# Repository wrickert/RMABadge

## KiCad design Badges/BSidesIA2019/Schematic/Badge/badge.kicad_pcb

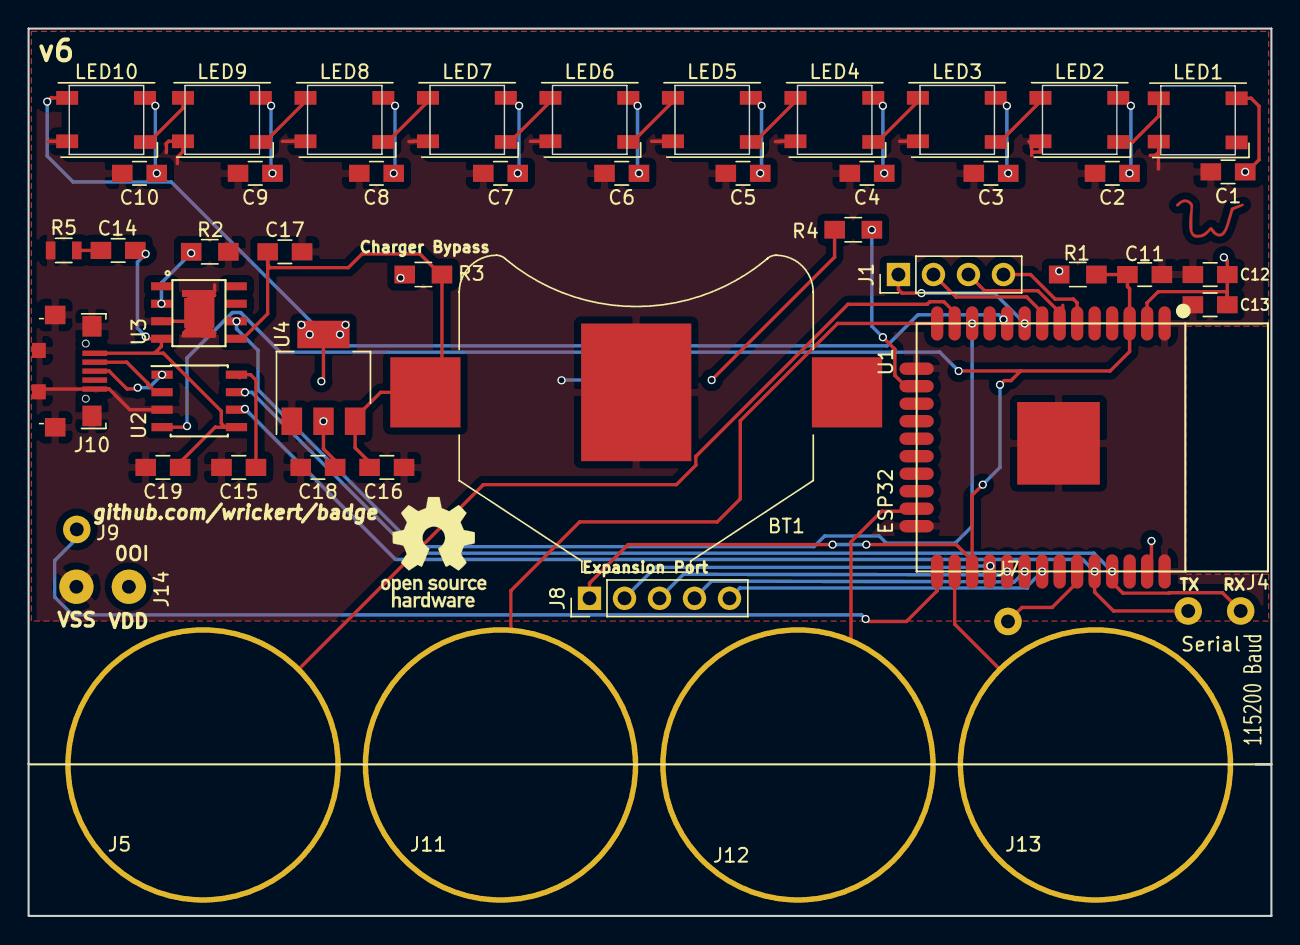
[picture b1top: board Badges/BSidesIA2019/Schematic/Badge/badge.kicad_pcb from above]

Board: 2 copper layers, 90.2 x 64.4 mm, 52 parts (1 on the bottom side), 39 nets.

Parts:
BT1: Battery_Cell; Keystone_3008_1x2450-CoinCell
C1, C2, C3, C4, C5, C6, C7, C8, C9, C10, C11, C12, C15, C19: 0.1uF; C_0805_HandSoldering
C13, C14, C17: 10uF; C_0805_HandSoldering
C16, C18: 1uF; C_0805_HandSoldering
J1: Left2; Pin_Header_Straight_1x04_Pitch2.54mm
J4: Serial; SolderWirePad_2x_1mmDrill
J5: Penny3; Penny
J7: Right2; SolderWirePad_single_1mmDrill
J8: Right3; Pin_Header_Straight_1x05_Pitch2.54mm
J9: Right4; SolderWirePad_single_1mmDrill
J10: USB_B_Micro; USB_Micro-B_Jing
J11: Penny2; Penny
J12: Penny1; Penny
J13: Penny0; Penny
J14: Power; SolderWirePad_2x_1mmDrill
LED1, LED2, LED3, LED4, LED5, LED6, LED7, LED8, LED9, LED10: WS2812B; WS2812B-Sunken
LS1: PKMCS0909E4000-R1; XDCR_PKMCS0909E4000-R1
R1: 10k; R_0805_HandSoldering
R2: 1k; R_0805_HandSoldering
R3: 0ohm; R_0805_HandSoldering
R4: 22ohm; R_0805_HandSoldering
R5: 1.5; R_0805
Ref**: Val**; W
U1: ESP32-WROOM
U2: otter_CH330; SOIC-8_3.9x4.9mm_Pitch1.27mm
U3: HX4056
U4: TLV1117-33; SOT-223-3_TabPin2

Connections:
IO0: J9.1, U1.25
IO5: J8.3, U1.29
IO13: R4.1, U1.16
IO17: J8.2, U1.28
IO18: J8.4, U1.30
IO19: J8.5, U1.31
IO21: J7.1, U1.33
IO27: U1.12, U3.6
IO32: J1.2, U1.8
IO33: J1.1, U1.9
IO34: J1.4, U1.6
IO35: J1.3, U1.7
unnamed: C14.1, R5.2
unnamed: C15.1, U2.8
unnamed: J10.2, U2.2
unnamed: J10.3, U2.1
unnamed: LED1.2, LED2.4
unnamed: LED2.2, LED3.4
unnamed: LED3.2, LED4.4
unnamed: LED4.2, LED5.4
unnamed: LED5.2, LED6.4
unnamed: LED6.2, LED7.4
unnamed: LED7.2, LED8.4
unnamed: LED8.2, LED9.4
unnamed: LED9.2, LED10.4
unnamed: LS1.1, R4.2
unnamed: R2.1, U3.2
P0: J13.1, U1.26
P1: J12.1, U1.23
P2: J11.1, U1.14
P3: J5.1, U1.13
RTS: C11.1, J8.1, R1.2, U1.3, U1.27, U2.4
RX: J4.1, U1.35, U2.7
SPI: LED10.2, U1.10
TX: J4.1, U1.34, U2.6
VBUS: C14.2, C19.2, J10.1, U2.5, U3.4
VDD: C1.1, C2.1, C3.1, C4.1, C5.1, C6.1, C7.1, C8.1, C9.1, C10.1, C12.2, C13.2, C18.1, J14.1, LED1.1, LED2.1, LED3.1, LED4.1, LED5.1, LED6.1, LED7.1, LED8.1, LED9.1, LED10.1, R1.1, R3.1, U1.2, U4.2
VDDA: BT1.1, C16.1, C17.2, R3.2, U3.5, U4.3
VSS: BT1.2, C1.2, C2.2, C3.2, C4.2, C5.2, C6.2, C7.2, C8.2, C9.2, C10.2, C11.2, C12.1, C13.1, C15.2, C16.2, C17.1, C18.2, C19.1, J10.5, J10.6, J14.1, LED1.3, LED2.3, LED3.3, LED4.3, LED5.3, LED6.3, LED7.3, LED8.3, LED9.3, LED10.3, LS1.2, R2.2, R5.1, U1.1, U1.15, U1.24, U1.38, U1.39, U2.3, U3.3, U3.9, U4.1

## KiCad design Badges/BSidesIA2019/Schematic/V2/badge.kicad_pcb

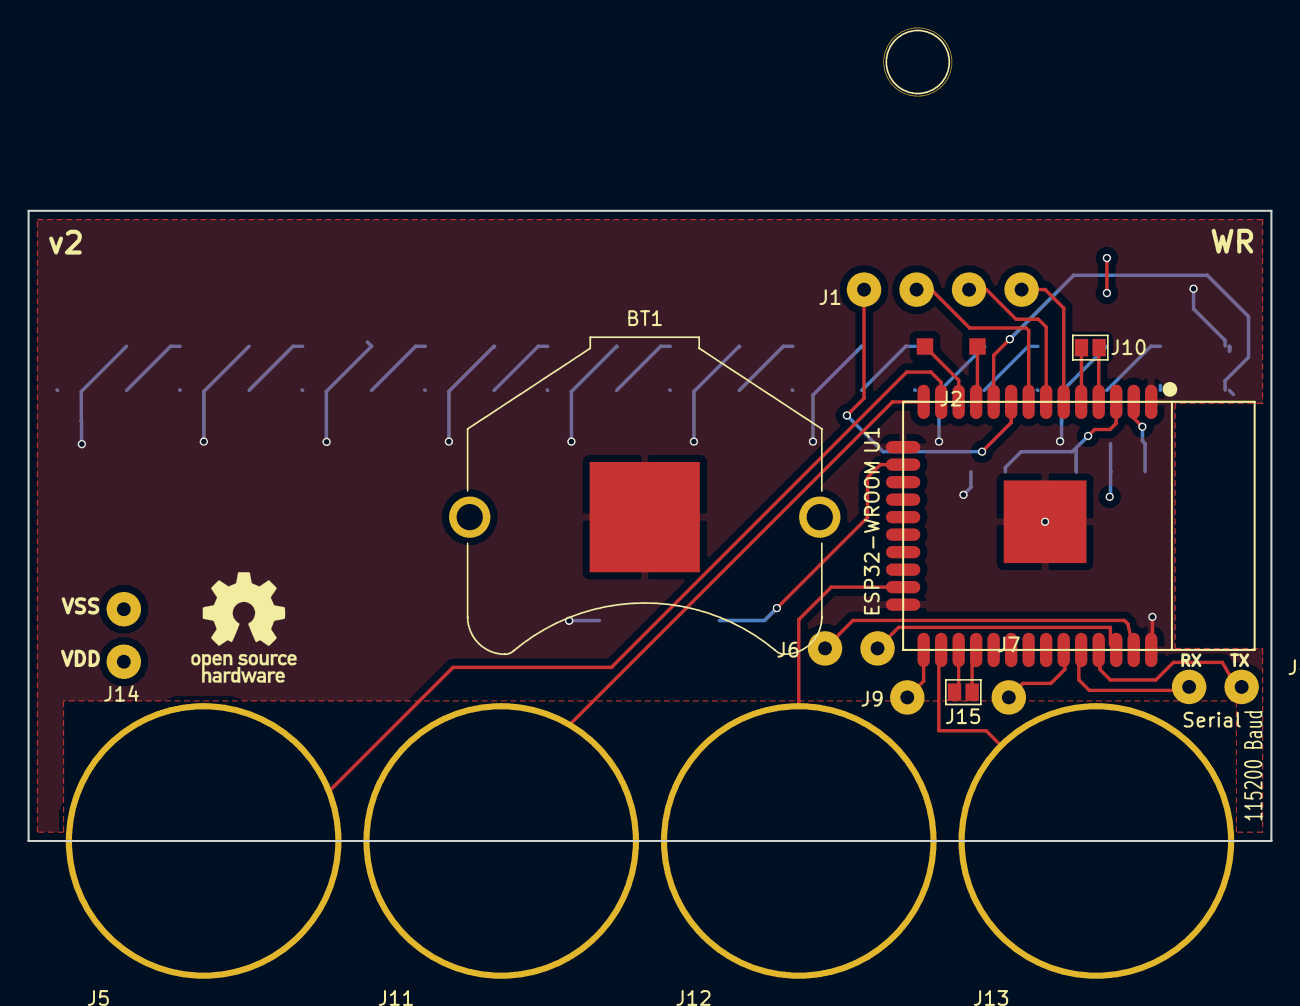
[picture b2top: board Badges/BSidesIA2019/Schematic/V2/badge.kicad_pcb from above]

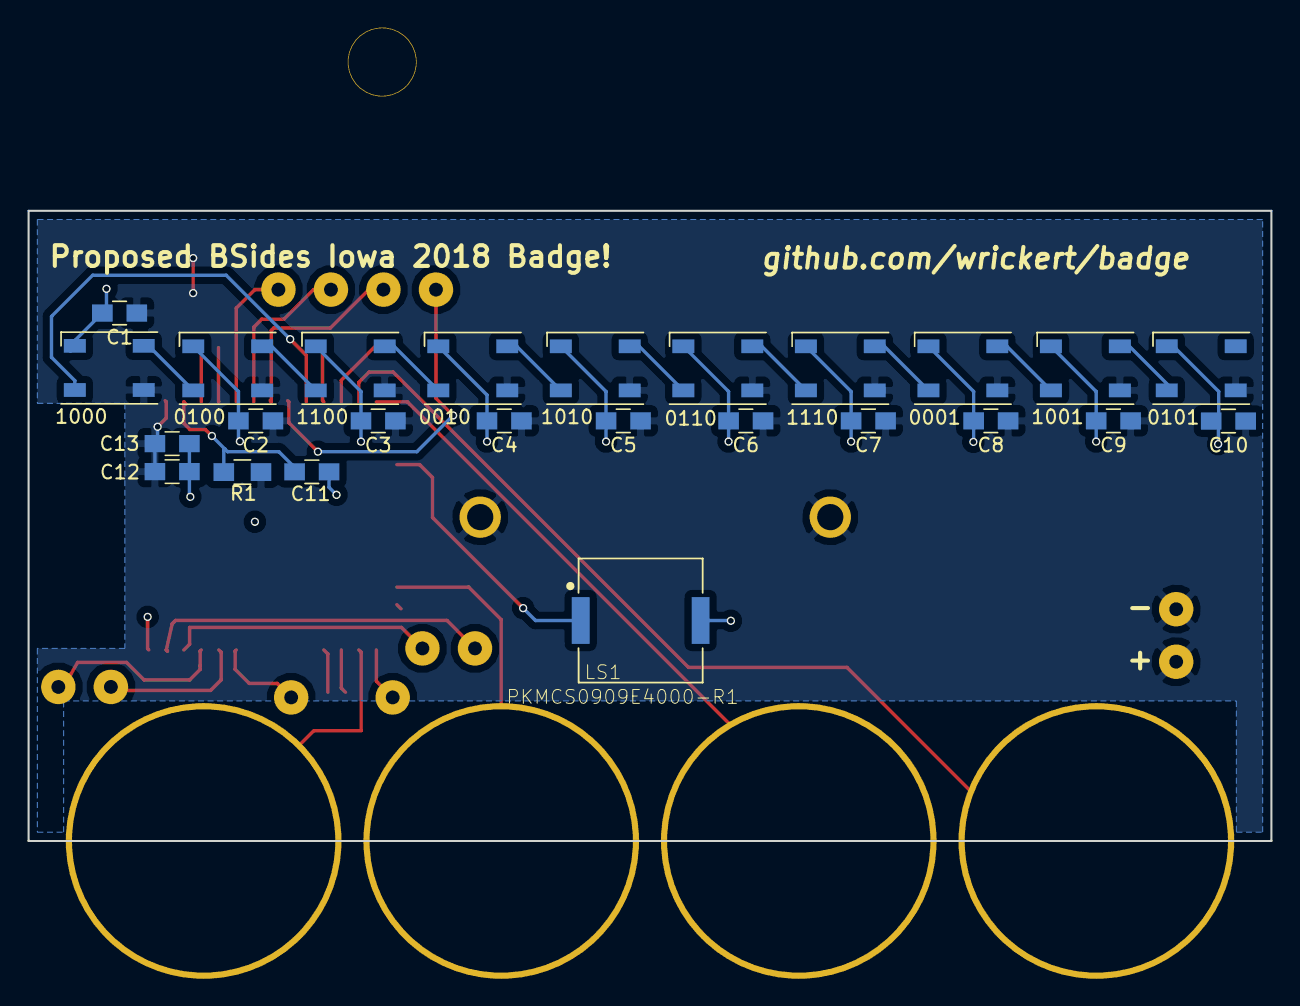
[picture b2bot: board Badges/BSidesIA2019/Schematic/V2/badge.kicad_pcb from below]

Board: 2 copper layers, 90.2 x 45.7 mm, 40 parts (25 on the bottom side), 35 nets.

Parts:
0001, 0010, 0100, 0101, 0110, 1000, 1001, 1010, 1100, 1110: WS2812B; LED_WS2812B-PLCC4
BT1: Battery_Cell; Keystone_3009_1x2450-CoinCell
C1, C2, C3, C4, C5, C6, C7, C8, C9, C10, C11, C12: 0.1uF; C_0805_HandSoldering
C13: 10uF; C_0805_HandSoldering
J1: Left2; SolderWirePad_4xInline_1mmDrill
J2: Left3; SolderWirePad_2x_1mmDrill
J4: Serial; SolderWirePad_2x_1mmDrill
J5: Penny3; Penny
J6: Right1; SolderWirePad_2x_1mmDrill
J7: Right2; SolderWirePad_single_1mmDrill
J9: Right4; SolderWirePad_single_1mmDrill
J10: Left1; GS2
J11: Penny2; Penny
J12: Penny1; Penny
J13: Penny0; Penny
J14: Power; SolderWirePad_2x_1mmDrill
J15: Right5; GS2
LS1: PKMCS0909E4000-R1; XDCR_PKMCS0909E4000-R1
R1: 10k; R_0805_HandSoldering
U1: ESP32-WROOM

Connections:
GND: C12.1, C13.1
IO0: J9.1, U1.25
IO13: LS1.1, U1.16
IO16: J15.2, U1.27
IO17: J15.1, U1.28
IO21: J7.1, U1.33
IO22: J6.1, U1.36
IO23: J6.1, U1.37
IO26: J2.1, U1.11
IO27: J2.1, U1.12
IO32: J1.1, U1.8
IO33: J1.1, U1.9
IO34: J1.1, U1.6
IO35: J1.1, U1.7
unnamed: C11.1, R1.2, U1.3
unnamed: 0100.4, 1000.2
unnamed: 0100.2, 1100.4
unnamed: 0010.4, 1100.2
unnamed: 0010.2, 1010.4
unnamed: 0110.4, 1010.2
unnamed: 0110.2, 1110.4
unnamed: 0001.4, 1110.2
unnamed: 0001.2, 1001.4
unnamed: 0101.4, 1001.2
P0: J13.1, U1.26
P1: J12.1, U1.23
P2: J11.1, U1.14
P3: J5.1, U1.13
RX: J4.1, U1.34
SPI: 1000.4, U1.10
TX: J4.1, U1.35
VDD: 0001.1, 0010.1, 0100.1, 0101.1, 0110.1, 1000.1, 1001.1, 1010.1, 1100.1, 1110.1, BT1.1, C1.1, C2.1, C3.1, C4.1, C5.1, C6.1, C7.1, C8.1, C9.1, C10.1, C12.2, C13.2, J14.1, R1.1, U1.2
VN: J10.1, U1.5
VP: J10.2, U1.4
VSS: 0001.3, 0010.3, 0100.3, 0101.3, 0110.3, 1000.3, 1001.3, 1010.3, 1100.3, 1110.3, BT1.2, C1.2, C2.2, C3.2, C4.2, C5.2, C6.2, C7.2, C8.2, C9.2, C10.2, C11.2, LS1.2, U1.1, U1.15, U1.24, U1.38, U1.39

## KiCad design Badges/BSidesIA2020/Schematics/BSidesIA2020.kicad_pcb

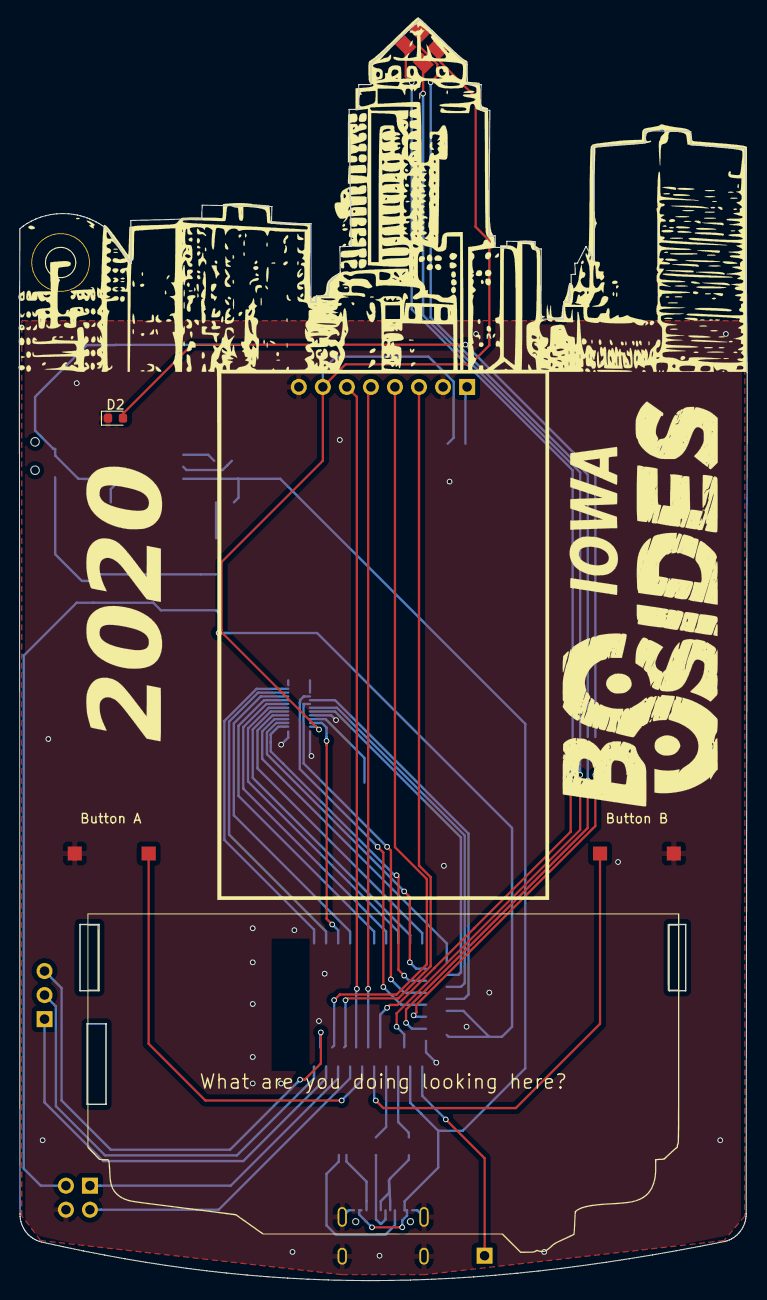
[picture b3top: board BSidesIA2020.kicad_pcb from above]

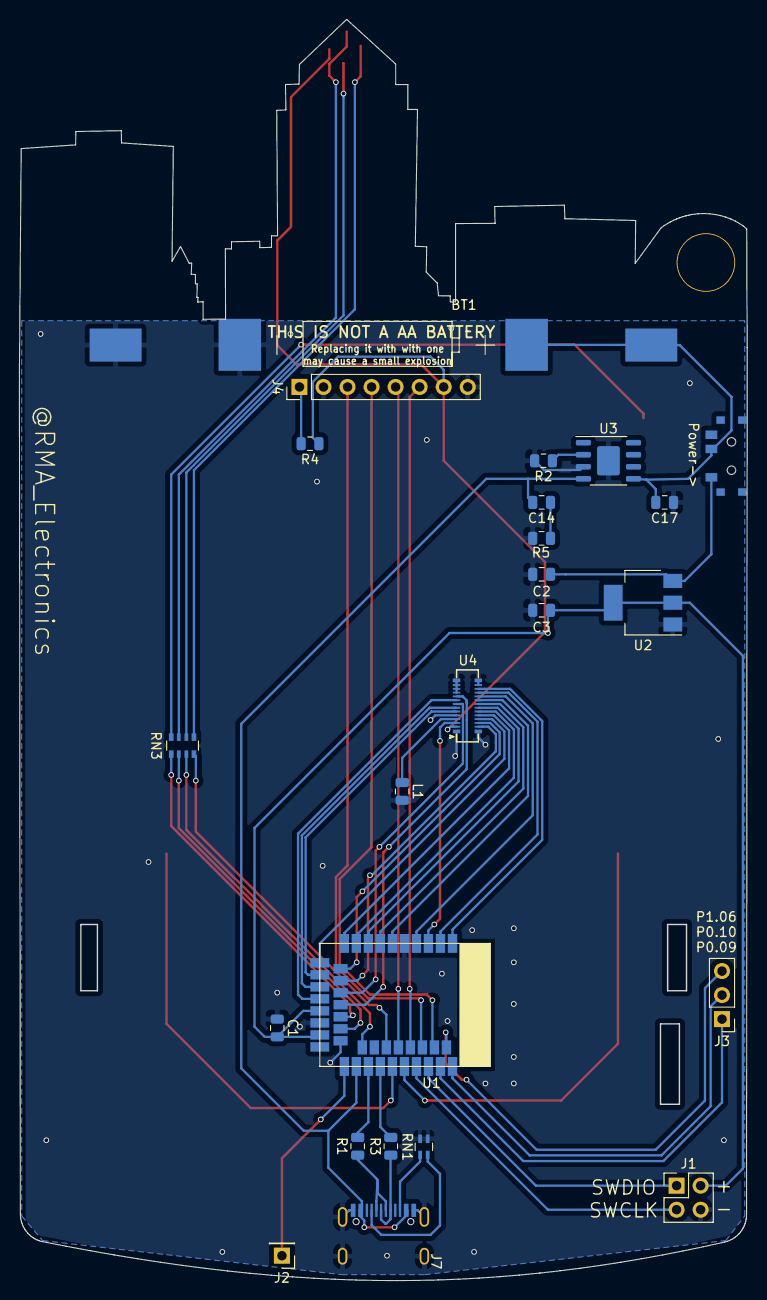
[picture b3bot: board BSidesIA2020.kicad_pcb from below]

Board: 2 copper layers, 76.9 x 133.3 mm, 28 parts (24 on the bottom side), 52 nets.

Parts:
BT1: Battery_Cell; Dongguan14500
Button A: SW_DIP_x01; 1TS002E-2500-2500-CT-HYP-Button
Button B: SW_DIP_x01; 1TS002E-2500-2500-CT-HYP-Button
C1: 4.7uF; C_0805_2012Metric
C2, C3: 1uF; C_0805_2012Metric
C14, C17: 10uF; C_0805_2012Metric
D1: LED_BGRA; EKINGLUX-E6
D2: LED; LED_0603_1608Metric
J1: Conn_02x02_Odd_Even; PinHeader_2x02_P2.54mm_Vertical
J2: Conn_01x01; PinHeader_1x01_P2.54mm_Vertical
J3: Conn_01x03; PinHeader_1x03_P2.54mm_Vertical
J4: Conn_01x08; PinHeader_1x08_P2.54mm_Vertical
J7: USB_C_Receptacle; USB_C_Receptical-Jing
L1: L_Small; L_0805_2012Metric
Power->: SW3; SK-3296S_switch
R1, R3: 27Ohm; R_0805_2012Metric
R2: 1k; R_0805_2012Metric
R4: R_Small; R_0805_2012Metric
R5: 1.5; R_0805_2012Metric
RN1: 10k; R_Array_Concave_2x0603
RN3: 270; R_Array_Convex_4x0603
U1: E73-2G4M08S1C
U2: TLV1117-33; SOT-223-3_TabPin2
U3: HX4056; HSOP-8-1EP_3.9x4.9mm_P1.27mm_EP2.41x3.1mm
U4: BBQ10KBD; BM14B(0.8)-24DS-0.4V(53)

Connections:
+5V: C14.2, J7.A4, J7.A9, J7.B4, J7.B9, U1.27, U3.4
Attention: RN3.1, U1.20
Blue: RN3.4, U1.32
ButtonA: Button A.2, U1.35
ButtonB: Button B.2, U1.33
COL1: U1.15, U4.7
COL2: U1.17, U4.9
COL3: U1.18, U4.10
COL4: U1.1, U4.17
COL5: U1.4, U4.19
D+: J7.A6, J7.B6, R3.1
D-: J7.A7, J7.B7, R1.1
DC: J4.3, U1.38
Green: RN3.3, U1.28
LEDA1: U1.12, U4.26
LEDA2: U1.10, U4.24
LEDK1: U1.11, U4.25
LEDK2: U1.9, U4.23
MIC: U1.3, U4.3
unnamed: C14.1, R5.2
unnamed: D1.1, RN3.5
unnamed: D1.2, RN3.6
unnamed: D1.3, RN3.7
unnamed: D2.2, RN3.8
unnamed: J2.1, U1.26
unnamed: J3.1, U1.41
unnamed: J3.2, U1.43
unnamed: J3.3, U1.42
unnamed: J4.1, R4.2
unnamed: J7.A5, RN1.2
unnamed: J7.B5, RN1.1
unnamed: L1.1, U4.4
unnamed: R1.2, U1.29
unnamed: R2.1, U3.2
unnamed: R3.2, U1.31
ROW1: U1.13, U4.6
ROW2: U1.16, U4.8
ROW3: U1.2, U4.18
ROW4: U1.6, U4.20
ROW5: U1.7, U4.21
ROW6: U1.8, U4.22
ROW7: U1.14, U4.27
RST: J4.4, U1.40
Red: RN3.2, U1.22
SCL: J4.6, U1.36
SDA: J4.5, U1.34
SWCLK: J1.1, U1.39
SWDIO: J1.3, U1.37
VCC: C1.2, C3.2, D1.4, J1.2, J4.7, R4.1, U1.19, U1.23, U2.2, U4.2
VDD: C2.2, Power->.3, U2.3
VDDA: BT1.1, C17.2, Power->.2, U3.5
VSS: BT1.2, Button A.1, Button B.1, C1.1, C2.1, C3.1, C17.1, D2.1, J1.4, J4.2, J4.8, J7.A1, J7.A12, J7.B1, J7.B12, J7.S1, L1.2, R2.2, R5.1, RN1.3, RN1.4, U1.5, U1.21, U1.24, U2.1, U3.3, U3.9, U4.1, U4.5, U4.11, U4.12, U4.13, U4.14, U4.15, U4.16, U4.28

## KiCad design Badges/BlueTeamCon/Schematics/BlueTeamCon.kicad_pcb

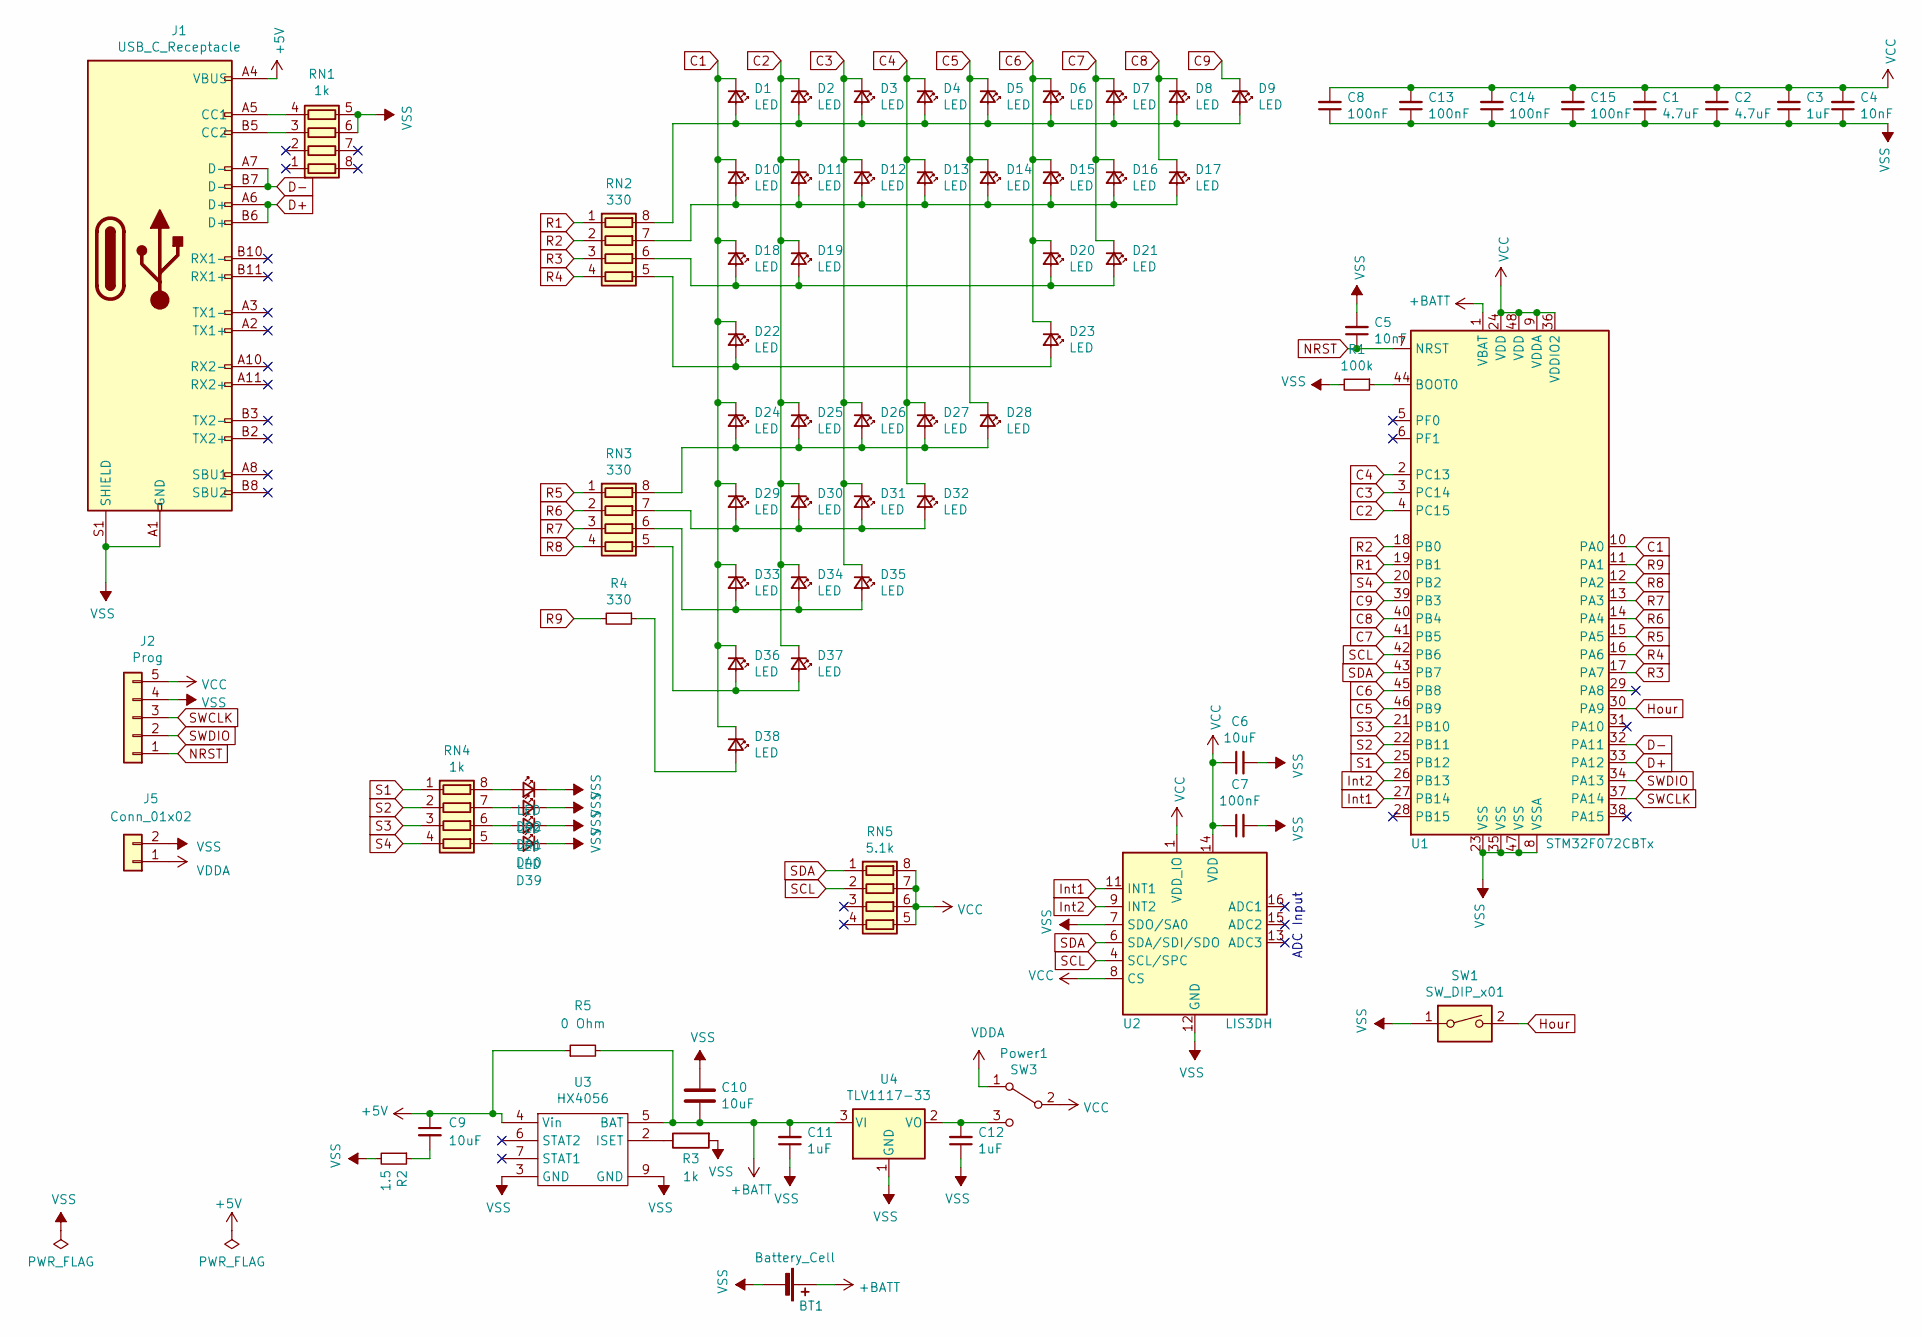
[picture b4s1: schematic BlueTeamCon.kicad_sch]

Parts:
BT1: Battery_Cell; Dongguan14500
C1, C2: 4.7uF; C_0805_2012Metric
C3, C11, C12: 1uF; C_0805_2012Metric
C4, C5: 10nF; C_0805_2012Metric
C6, C9, C10: 10uF; C_0805_2012Metric
C7, C8, C13, C14, C15: 100nF; C_0805_2012Metric
D1, D2, D3, D4, D5, D6, D7, D8, D9, D10, D11, D12, D13, D14, D15, D16, D17, D18, D19, D20, D21, D22, D23, D24, D25, D26, D27, D28, D29, D30, D31, D32, D33, D34, D35, D36, D37, D38: LED; LED_0805_2012Metric
D39, D40, D41, D42: LED; T776-ReverseMountLED
J1: USB_C_Receptacle; USB_C_Receptical-Jing
J2: Prog; PinHeader_1x05_P2.54mm_Vertical
J5: Conn_01x02; PinHeader_1x02_P2.54mm_Vertical
Power1: SW3; SK-3296S_switch
R1: 100k; R_0805_2012Metric
R2: 1.5; R_0805_2012Metric
R3: 1k; R_0805_2012Metric
R4: 330; R_0805_2012Metric
R5: 0 Ohm; R_0805_2012Metric
RN1, RN4: 1k; R_Array_Convex_4x0603
RN2, RN3: 330; R_Array_Convex_4x0603
RN5: 5.1k; R_Array_Convex_4x0603
SW1: SW_DIP_x01; SW_SPST_SKQG_WithStem
U1: STM32F072CBTx; LQFP-48_7x7mm_P0.5mm
U2: LIS3DH; LGA-16_3x3mm_P0.5mm_LayoutBorder3x5y
U3: HX4056; HTSOP-8-1EP_3.9x4.9mm_P1.27mm_EP2.4x3.2mm
U4: TLV1117-33; SOT-223-3_TabPin2

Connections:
+5V: C9.1, J1.A4 (VBUS), J1.A9 (VBUS), J1.B4 (VBUS), J1.B9 (VBUS), R5.1, U3.4 (Vin)
+BATT: BT1.1 (+), C10.2, C11.2, R5.2, U1.1 (VBAT), U3.5 (BAT), U4.3 (VI)
C1: D1.1 (K), D10.1 (K), D18.1 (K), D22.1 (K), D24.1 (K), D29.1 (K), D33.1 (K), D36.1 (K), D38.1 (K), U1.10 (PA0)
C2: D2.1 (K), D11.1 (K), D19.1 (K), D25.1 (K), D30.1 (K), D34.1 (K), D37.1 (K), U1.4 (PC15)
C3: D3.1 (K), D12.1 (K), D26.1 (K), D31.1 (K), D35.1 (K), U1.3 (PC14)
C4: D4.1 (K), D13.1 (K), D27.1 (K), D32.1 (K), U1.2 (PC13)
C5: D5.1 (K), D14.1 (K), D28.1 (K), U1.46 (PB9)
C6: D6.1 (K), D15.1 (K), D20.1 (K), D23.1 (K), U1.45 (PB8)
C7: D7.1 (K), D16.1 (K), D21.1 (K), U1.41 (PB5)
C8: D8.1 (K), D17.1 (K), U1.40 (PB4)
C9: D9.1 (K), U1.39 (PB3)
D+: J1.A6 (D+), J1.B6 (D+), U1.33 (PA12)
D-: J1.A7 (D-), J1.B7 (D-), U1.32 (PA11)
Hour: SW1.2, U1.30 (PA9)
Int1: U1.27 (PB14), U2.11 (INT1)
Int2: U1.26 (PB13), U2.9 (INT2)
NRST: C5.1, J2.1, U1.7 (NRST)
unnamed: C9.2, R2.1
unnamed: C12.2, Power1.3 (C), U4.2 (VO)
unnamed: D1.2 (A), D2.2 (A), D3.2 (A), D4.2 (A), D5.2 (A), D6.2 (A), D7.2 (A), D8.2 (A), D9.2 (A), RN2.8 (R1.2)
unnamed: D10.2 (A), D11.2 (A), D12.2 (A), D13.2 (A), D14.2 (A), D15.2 (A), D16.2 (A), D17.2 (A), RN2.7 (R2.2)
unnamed: D18.2 (A), D19.2 (A), D20.2 (A), D21.2 (A), RN2.6 (R3.2)
unnamed: D22.2 (A), D23.2 (A), RN2.5 (R4.2)
unnamed: D24.2 (A), D25.2 (A), D26.2 (A), D27.2 (A), D28.2 (A), RN3.8 (R1.2)
unnamed: D29.2 (A), D30.2 (A), D31.2 (A), D32.2 (A), RN3.7 (R2.2)
unnamed: D33.2 (A), D34.2 (A), D35.2 (A), RN3.6 (R3.2)
unnamed: D36.2 (A), D37.2 (A), RN3.5 (R4.2)
unnamed: D38.2 (A), R4.1
unnamed: D39.2 (A), RN4.5 (R4.2)
unnamed: D40.2 (A), RN4.6 (R3.2)
unnamed: D41.2 (A), RN4.7 (R2.2)
unnamed: D42.2 (A), RN4.8 (R1.2)
unnamed: J1.A5 (CC1), RN1.4 (R4.1)
unnamed: J1.B5 (CC2), RN1.3 (R3.1)
unnamed: R1.1, U1.44 (BOOT0)
unnamed: R3.1, U3.2 (ISET)
R1: RN2.1 (R1.1), U1.19 (PB1)
R2: RN2.2 (R2.1), U1.18 (PB0)
R3: RN2.3 (R3.1), U1.17 (PA7)
R4: RN2.4 (R4.1), U1.16 (PA6)
R5: RN3.1 (R1.1), U1.15 (PA5)
R6: RN3.2 (R2.1), U1.14 (PA4)
R7: RN3.3 (R3.1), U1.13 (PA3)
R8: RN3.4 (R4.1), U1.12 (PA2)
R9: R4.2, U1.11 (PA1)
S1: RN4.1 (R1.1), U1.25 (PB12)
S2: RN4.2 (R2.1), U1.22 (PB11)
S3: RN4.3 (R3.1), U1.21 (PB10)
S4: RN4.4 (R4.1), U1.20 (PB2)
SCL: RN5.2 (R2.1), U1.42 (PB6), U2.4 (SCL/SPC)
SDA: RN5.1 (R1.1), U1.43 (PB7), U2.6 (SDA/SDI/SDO)
SWCLK: J2.3, U1.37 (PA14)
SWDIO: J2.2, U1.34 (PA13)
VCC: C1.2, C2.2, C3.2, C4.2, C6.1, C7.1, C8.2, C13.2, C14.2, C15.2, J2.5, Power1.2 (B), RN5.5 (R4.2), RN5.6 (R3.2), RN5.7 (R2.2), RN5.8 (R1.2), U1.9 (VDDA), U1.24 (VDD), U1.36 (VDDIO2), U1.48 (VDD), U2.1 (VDD_IO), U2.8 (CS), U2.14 (VDD)
VDDA: J5.1, Power1.1 (A)
VSS: BT1.2 (-), C1.1, C2.1, C3.1, C4.1, C5.2, C6.2, C7.2, C8.1, C10.1, C11.1, C12.1, C13.1, C14.1, C15.1, D39.1 (K), D40.1 (K), D41.1 (K), D42.1 (K), J1.A1 (GND), J1.A12 (GND), J1.B1 (GND), J1.B12 (GND), J1.S1 (SHIELD), J2.4, J5.2, R1.2, R2.2, R3.2, RN1.5 (R4.2), RN1.6 (R3.2), SW1.1, U1.8 (VSSA), U1.23 (VSS), U1.35 (VSS), U1.47 (VSS), U2.5 (GND), U2.7 (SDO/SA0), U2.10 (GND), U2.12 (GND), U3.3 (GND), U3.9 (GND), U4.1 (GND)

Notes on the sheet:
ADC Input

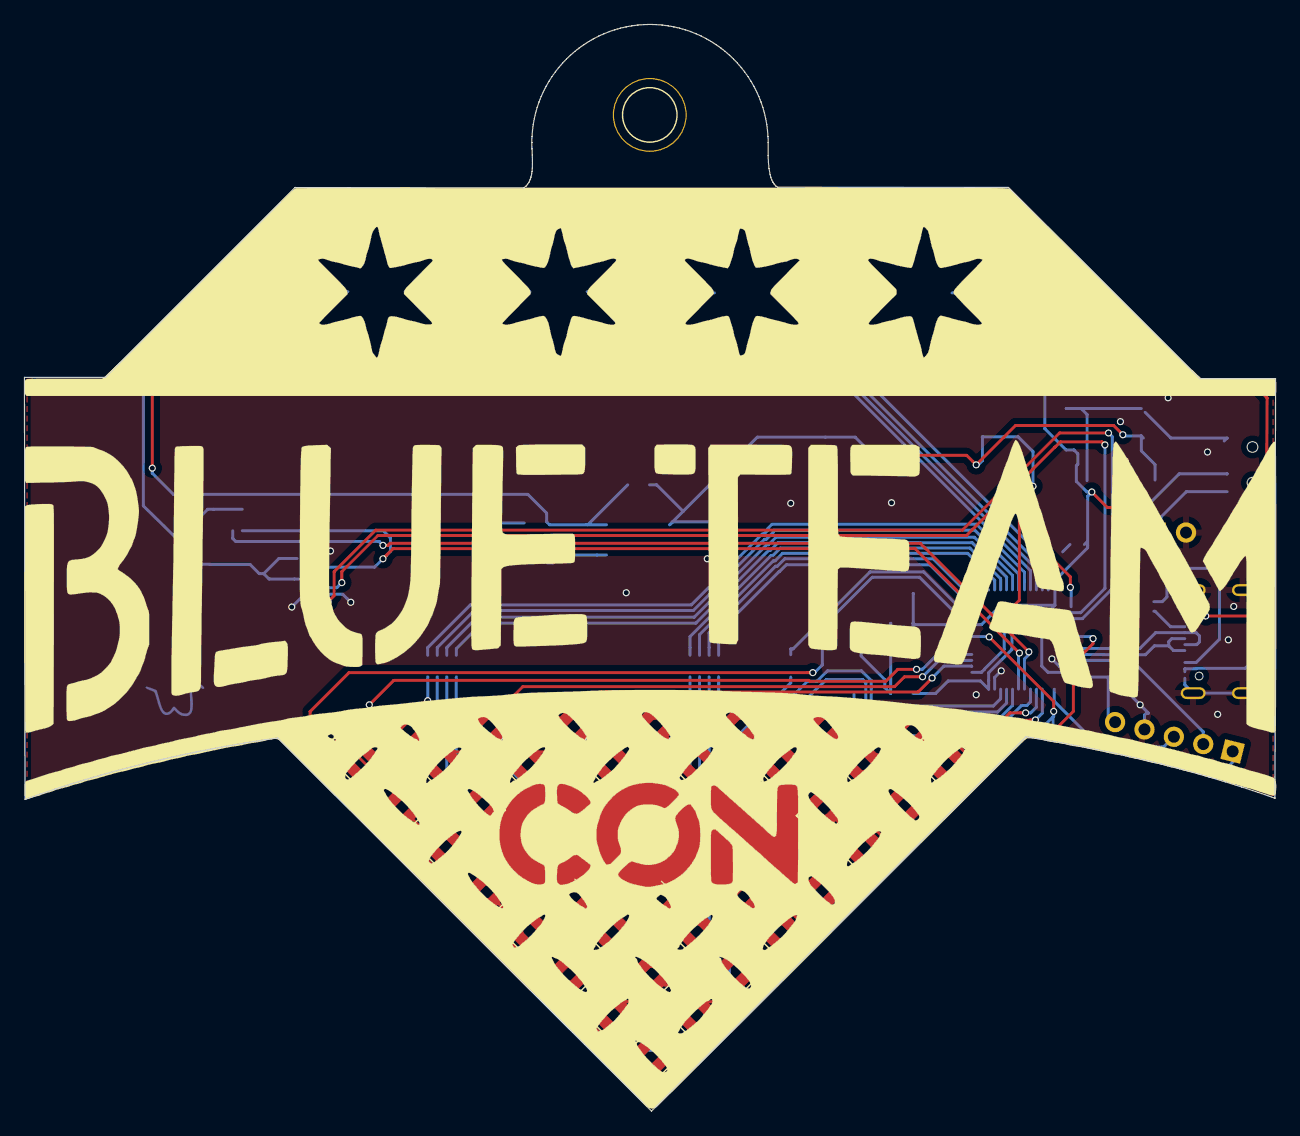
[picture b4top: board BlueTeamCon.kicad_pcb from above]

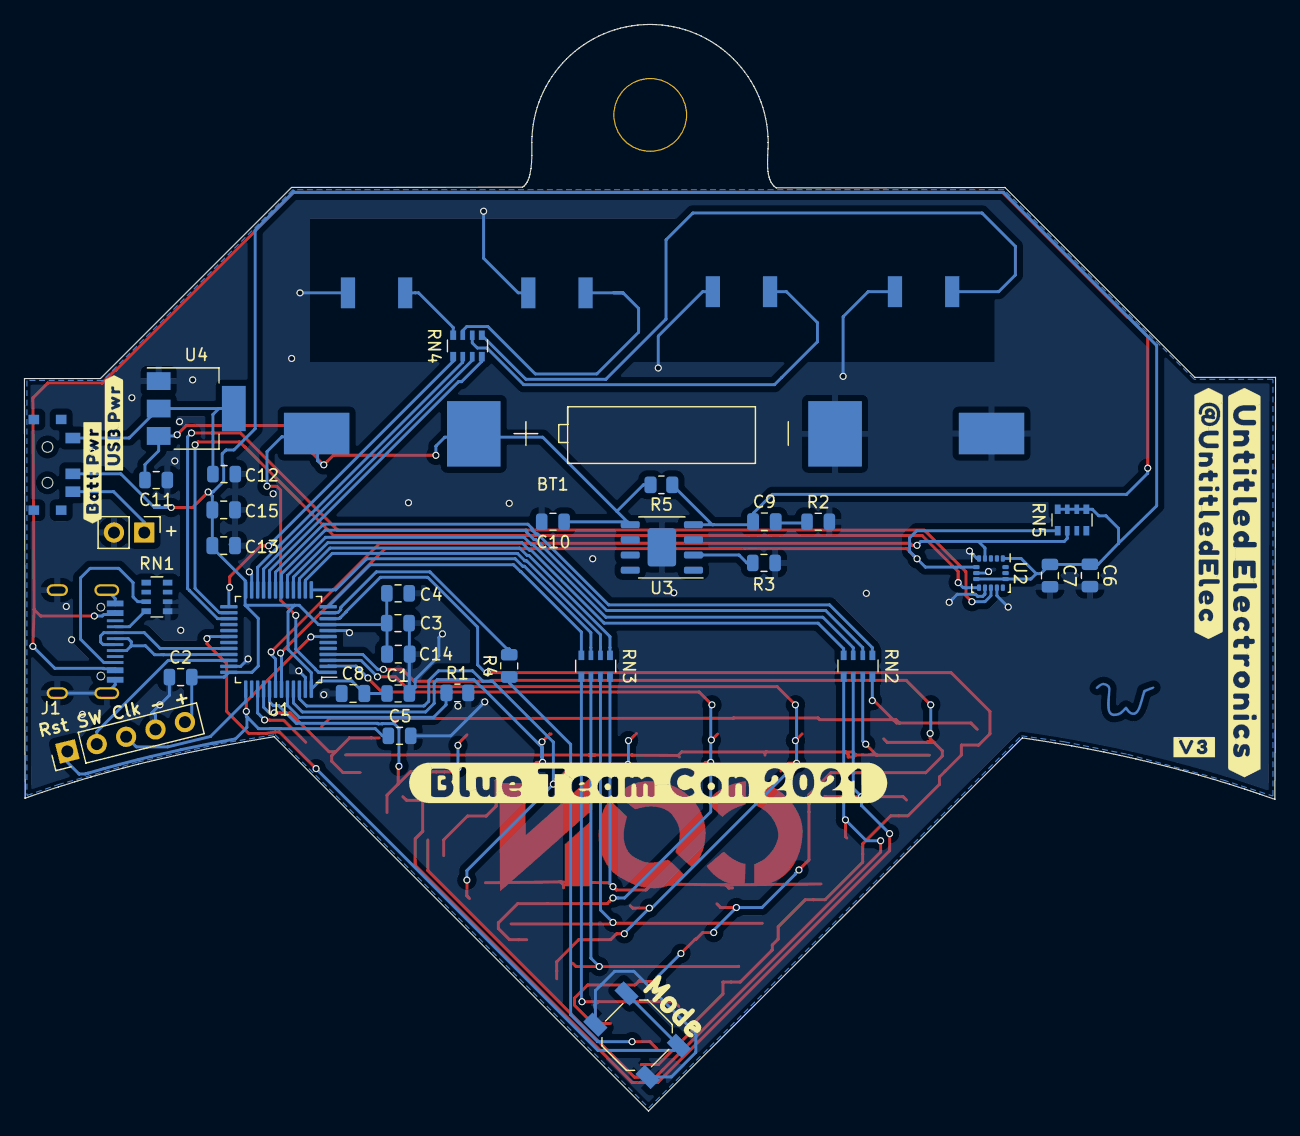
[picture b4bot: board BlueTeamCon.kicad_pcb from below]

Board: 2 copper layers, 104.9 x 91.1 mm, 78 parts (40 on the bottom side), 56 nets.

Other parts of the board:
Ref**: Val**; W
